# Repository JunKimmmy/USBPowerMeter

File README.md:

# USB-C Power Meter

A compact USB-C passthrough power meter that displays real-time voltage, current, and power on an integrated 128×64 OLED screen. It sits inline between a USB-C charger and a device — all USB signals pass through transparently while the onboard MCU samples the INA238 power monitor and drives the display.

---

## Features

- **Real-time readout** — voltage, current, and power updated continuously
- **Rolling graphs** — 128-sample circular-buffer plots for current and power with live, average, and peak annotations
- **Running averages** — displayed in the footer of the main meter screen
- **Boot animation** and **dancing-banana easter egg**
- **Buzzer** with user-configurable tones and mute toggle
- **Power switch** and **navigation buttons** for menu control
- Full USB-C signal passthrough (VBUS + data lines)

---

## Specifications

| Parameter | Value |
|-----------|-------|
| Input voltage range | 0.3 V – 48 V |
| Max continuous current | 5 A |
| ADC resolution | 16-bit (INA238) |
| Display | 128×64 OLED (SSD1315), I²C |
| MCU | STM32G030K6T6 (LQFP-32) |
| MCU/peripheral supply | 3.3 V buck from VBUS |
| OLED supply | 3.8 V boost |
| Passthrough | USB-C male + USB-C female |

---

## PCB

Designed in **KiCad 10**. All custom symbols and footprints are in `libs/`.

### Key ICs

| IC | Function |
|----|----------|
| INA238 | 16-bit high-precision power/current/voltage monitor (shunt + bus voltage) |
| STM32G030K6T6 | Measurement processing, graph engine, display control |
| SSD1315 | 128×64 OLED controller (I²C) |
| LMR36006 | VBUS-to-3.3 V synchronous buck regulator |
| DGS0010A | 3.8 V boost supply for OLED |

---

## Enclosure

3D-printable enclosure designed in OnShape:
[View in OnShape](https://cad.onshape.com/documents/12768789c7e8d715e02a9c44/w/91224a42db391f032592c489/e/40e560f0614cc0d05faddfcd?renderMode=0&uiState=6a30851d7d6de7ff176b633c)

---

## Build Process

All components were **hand-soldered**. Firmware was flashed over SWD using an **ST-Link V3 Mini**.

### Videos

| Video | Description |
|-------|-------------|
| [PCB Assembly](videos/pcb-assembly.mp4) | Hand-soldering all components onto the board |
| [Display Testing](videos/display-testing.mp4) | OLED display bring-up and meter UI |
| [Buzzer Testing](videos/buzzer-testing.mp4) | Buzzer tone testing |

---

## Testing

The meter was tested by powering a **mini hotplate** (~20 V supply). The power graph clearly shows the hotplate's heating element ramping up linearly from 0 W as it heats, plateauing around **42 W** once it reaches temperature, then dropping sharply when switched off.

---

## Firmware

Written in C using STM32CubeIDE with the STM32 HAL. Targets the STM32G030K6T6.

### Display Modes

| Mode | Description |
|------|-------------|
| **Main Meter** | Two-column header (VOLT / AMPS), large 2× readout, full-width power row, footer with running averages |
| **Current Graph** | 128-sample rolling plot of current (mA), dashed line = running average, header shows live + avg + peak |
| **Power Graph** | Same layout as current graph but for power (mW) |

Navigate between modes with the onboard buttons.

### Source Modules

| File | Purpose |
|------|---------|
| `main.c` | HAL init, main loop, buzzer tone engine |
| `meter.c` | Display screens, graph circular buffer, button debounce |
| `oled.c` | SSD1315 OLED driver (I²C, page-mode framebuffer) |
| `ina238.c` | INA238 driver — shunt/bus voltage, current, power registers |
| `boot.c` | Animated boot screen |
| `banana.c / banana_frames.c` | Dancing-banana easter egg animation |
| `generate_frames.py` | Converts 249×246 GIF PROGMEM bitmaps to SSD1315 page-format C arrays |

### Building & Flashing

1. Open `Firmware/ST/` in **STM32CubeIDE**
2. Build (Ctrl+B) — targets STM32G030K6T6, `STM32G030K6TX_FLASH.ld`
3. Connect **ST-Link V3 Mini** to the SWD header and flash

---

## Repository Structure

```
USBpowermeter.kicad_pro       KiCad project
USBpowermeter.kicad_sch       Schematic
USBpowermeter.kicad_pcb       PCB layout
libs/
  Library.kicad_sym           Custom schematic symbols
  Library.pretty/             Custom footprints
  3dmodels/                   STEP models for 3D viewer
Firmware/ST/
  Core/Src/                   Application source (C)
  Core/Inc/                   Application headers
  Drivers/                    STM32 HAL + CMSIS
  generate_frames.py          Bitmap conversion tool
images/                       PCB renders, enclosure CAD, real photos
videos/                       Assembly and testing footage
```

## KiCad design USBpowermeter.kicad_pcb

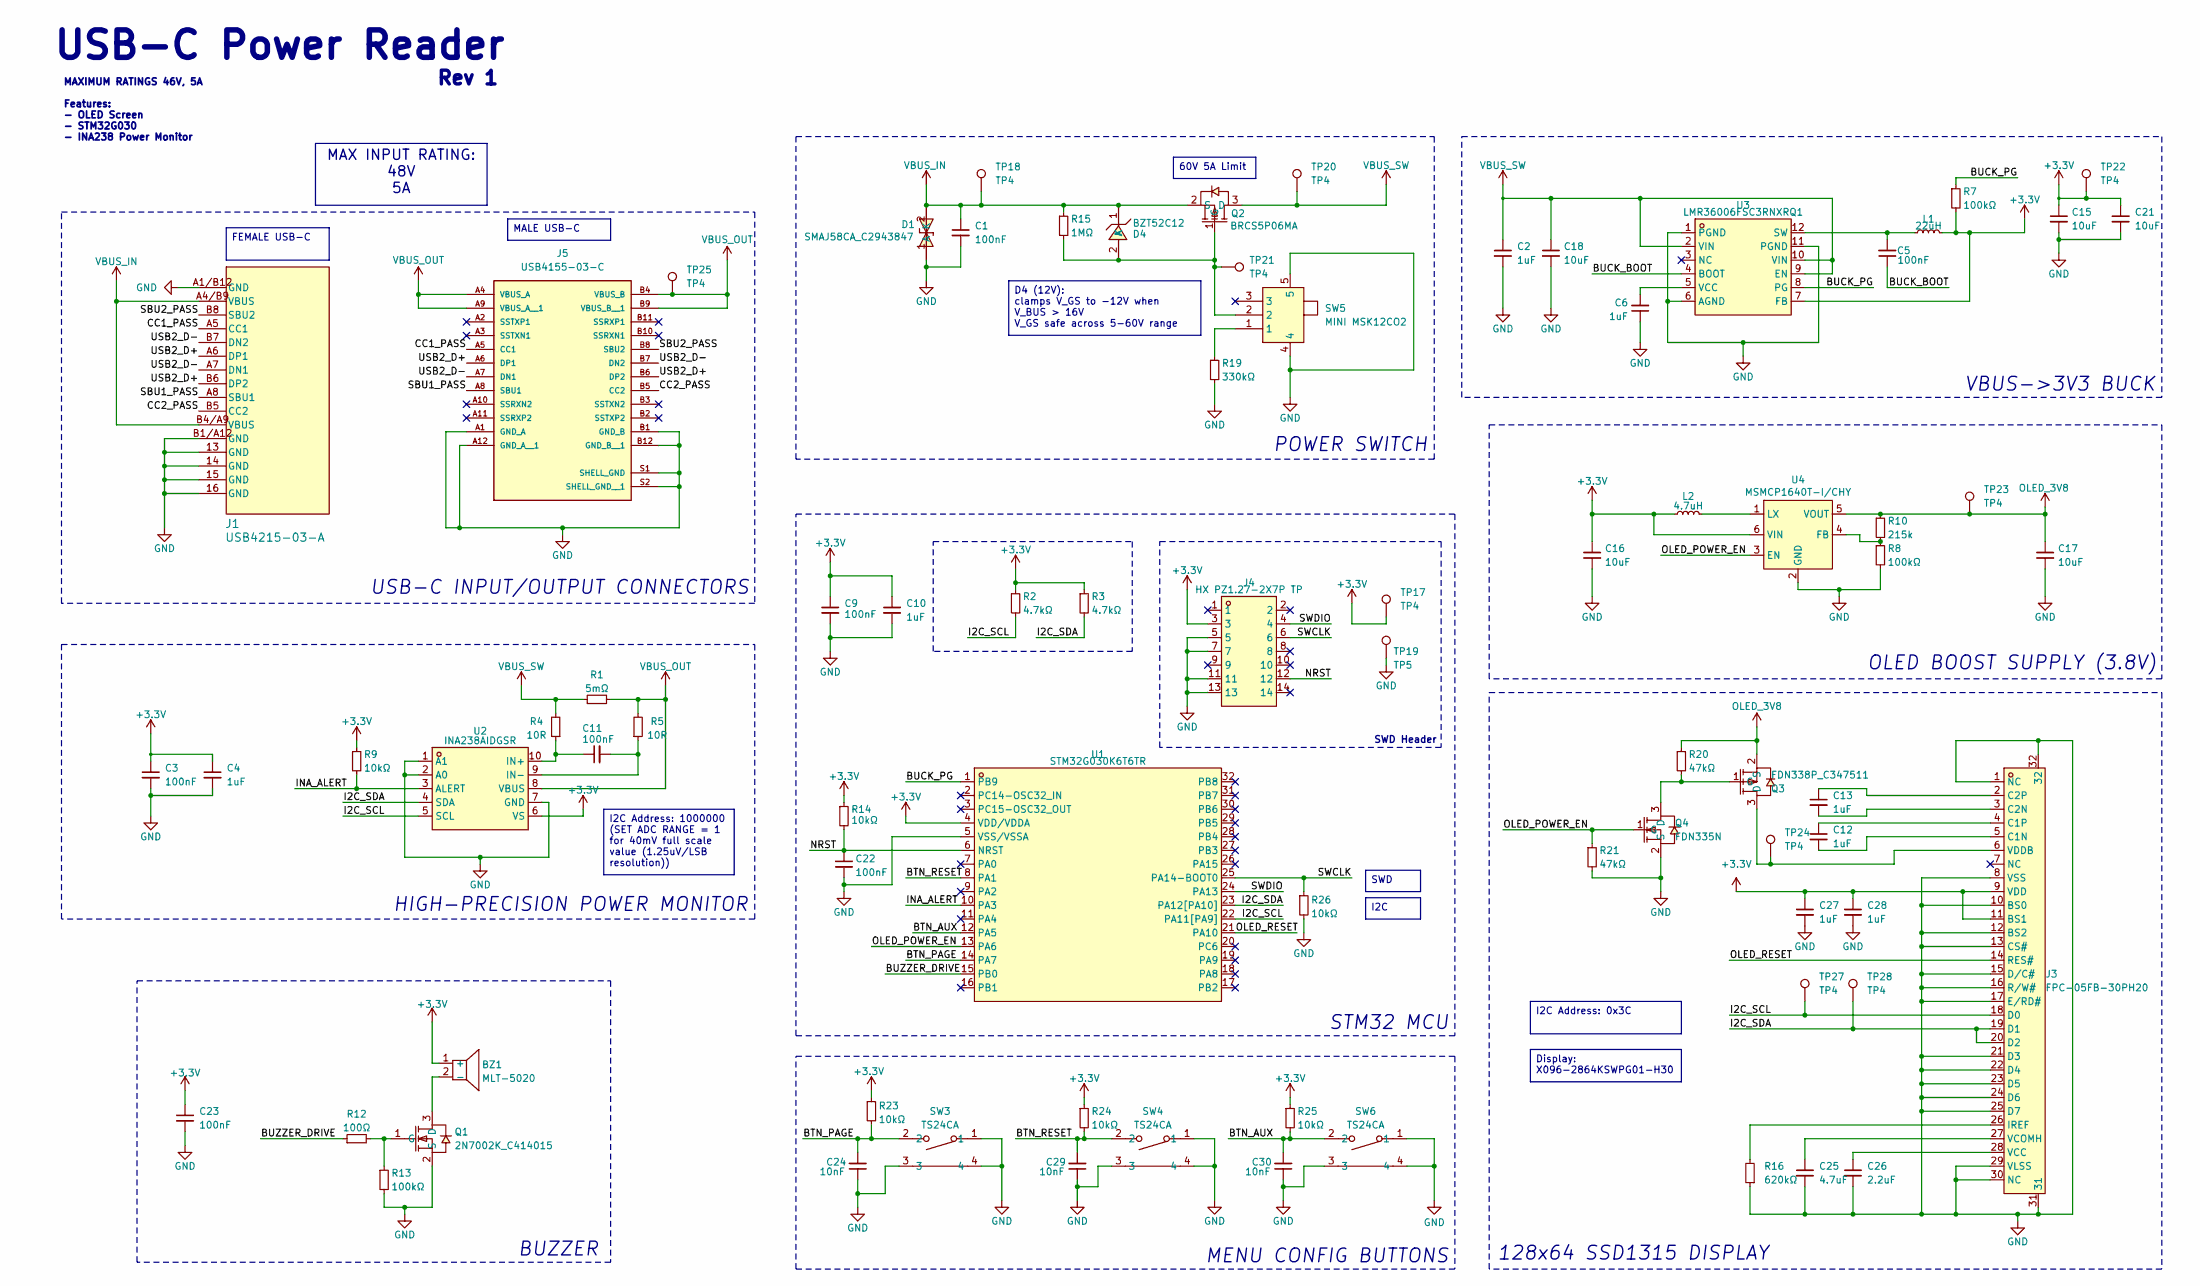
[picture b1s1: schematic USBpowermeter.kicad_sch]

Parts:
BZ1: MLT-5020; BUZ-SMD_L5.0-W5.5-P4.60; LCSC Part C94598
C1: 100nF; C_0603_1608Metric; LCSC Part C77058
C2, C4, C6, C10, C12, C13, C27, C28: 1uF; C_0402_1005Metric; LCSC Part C42371686
C3, C5, C9, C11, C22, C23: 100nF; C_0402_1005Metric; LCSC Part C343042
C15, C16, C17, C21: 10uF; C_0402_1005Metric; LCSC Part C15525
C18: 10uF; C_0805_2012Metric; LCSC Part C22367830
C24, C29, C30: 10nF; C_0402_1005Metric; LCSC Part C22400107
C25: 4.7uF; C_0402_1005Metric; LCSC Part C318563
C26: 2.2uF; C_0402_1005Metric; LCSC Part C12530
D1: SMAJ58CA_C2943847; SMA_L4.2-W2.6-LS5.0-BI; LCSC Part C148235
D4: BZT52C12; SOD-123_L2.7-W1.6-LS3.7-RD; LCSC Part C19077410
J1: USB4215-03-A; CONN_8p94X6p5X3p16_12L_GCC; LCSC Part C37616412
J3: FPC-05FB-30PH20; FPC-SMD_30P-P0.50_FPC-05FB-30PH20; LCSC Part C2856833
J4: HX PZ1.27-2X7P TP; HDR-SMD_14P-P1.27_HX-PZ1.27-2X7P-TP; LCSC Part C41376039
J5: USB4155-03-C; GCT_USB4155-03-C_REVA; PARTREV A; LCSC Part ORDER ON DIGIKEY
L1: 22uH; L_APV_ANR3015; LCSC Part C6364792
L2: 4.7uH; L_0603_1608Metric; LCSC Part C295681
Q1: 2N7002K_C414015; SOT-23-3; LCSC Part C8545
Q2: BRCS5P06MA; SOT-23-3_L2.9-W1.3-P1.90-LS2.4-BR; LCSC Part C914070
Q3: FDN338P_C347511; SOT-23-3; LCSC Part C24855
Q4: FDN335N; SOT-23-3; LCSC Part C241804
R1: 5mΩ; R_1206_3216Metric; LCSC Part C2988648
R2, R3: 4.7kΩ; R_0402_1005Metric; LCSC Part C105871
R4, R5: 10R; R_0402_1005Metric; LCSC Part C2906862
R7, R8, R13: 100kΩ; R_0402_1005Metric; LCSC Part C2906859
R9, R14, R23, R24, R25, R26: 10kΩ; R_0402_1005Metric; LCSC Part C2906861
R10: 215k; R_0402_1005Metric; LCSC Part C3013158
R12: 100Ω; R_0402_1005Metric; LCSC Part C2906860
R15: 1MΩ; R_0402_1005Metric; LCSC Part C2909328
R16: 620kΩ; R_0402_1005Metric; LCSC Part C2909373
R19: 330kΩ; R_0402_1005Metric; LCSC Part C2909349
R20, R21: 47kΩ; R_0402_1005Metric; LCSC Part C2906872
SW3, SW4, SW6: TS24CA; SW-SMD_2P-TS24CA; LCSC Part C393942
SW5: MINI MSK12CO2; SW-SMD_MSK12CO2; LCSC Part C2681570
TP17, TP18, TP20, TP21, TP22, TP23, TP24, TP25, TP27, TP28: TP4; TestPoint_Pad_D1.0mm
TP19: TP5; TestPoint_Pad_D1.0mm
U1: STM32G030K6T6TR; LQFP-32_L7.0-W7.0-P0.80-LS9.0-BL; LCSC Part C724043
U2: INA238AIDGSR; VSSOP-10_L3.0-W3.0-P0.50-LS4.9-BL; LCSC Part C2868250
U3: LMR36006FSC3RNXRQ1; VQFN-12_L3.0-W2.0-P0.65-BL_TI_RNX; LCSC Part C1850337
U4: MSMCP1640T-I/CHY; SOT-23-6; LCSC Part C49208392

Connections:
+3.3V: BZ1.1 (+), C3.1, C4.1, C9.1, C10.1, C15.1, C16.1, C21.1, C23.1, C27.1, C28.1, J3.9 (VDD), J3.11 (BS1), J4.3, L1.2, L2.1, R2.1, R3.1, R7.2, R9.1, R14.1, R23.1, R24.1, R25.1, TP17.1, TP22.1 (1_1), U1.4 (VDD/VDDA), U2.6 (VS), U3.7 (FB), U4.6 (VIN)
/BTN_AUX: C30.2, R25.2, SW6.2, U1.12 (PA5)
/BTN_PAGE: C24.2, R23.2, SW3.2, U1.14 (PA7)
/BTN_RESET: C29.2, R24.2, SW4.2, U1.8 (PA1)
/BUCK_BOOT: C5.1, U3.4 (BOOT)
/BUCK_PG: R7.1, U1.1 (PB9), U3.8 (PG)
/BUZZER_DRIVE: R12.1, U1.15 (PB0)
/CC1_PASS: J1.A5 (CC1), J5.A5 (CC1)
/CC2_PASS: J1.B5 (CC2), J5.B5 (CC2)
/I2C_SCL: J3.18 (D0), R2.2, TP27.1 (1_1), U1.22 (PA11[PA9]), U2.5 (SCL)
/I2C_SDA: J3.19 (D1), J3.20 (D2), R3.2, TP28.1 (1_1), U1.23 (PA12[PA10]), U2.4 (SDA)
/INA_ALERT: R9.2, U1.10 (PA3), U2.3 (ALERT)
/NRST: C22.1, J4.12, R14.2, U1.6 (NRST)
/OLED_POWER_EN: Q4.1 (G), R21.1, U1.13 (PA6), U4.3 (EN)
/OLED_RESET: J3.14 (RES#), U1.21 (PA10)
/SBU1_PASS: J1.A8 (SBU1), J5.A8 (SBU1)
/SBU2_PASS: J1.B8 (SBU2), J5.B8 (SBU2)
/SWCLK: J4.6, R26.1, U1.25 (PA14-BOOT0)
/SWDIO: J4.4, U1.24 (PA13)
/USB2_D+: J1.A6 (DP1), J1.B6 (DP2), J5.A6 (DP1), J5.B6 (DP2)
/USB2_D-: J1.A7 (DN1), J1.B7 (DN2), J5.A7 (DN1), J5.B7 (DN2)
GND: C1.2, C2.2, C3.2, C4.2, C6.1, C9.2, C10.2, C15.2, C16.2, C17.2, C18.2, C21.2, C22.2, C23.2, C24.1, C25.2, C26.2, C27.2, C28.2, C29.1, C30.1, D1.1 (K), J1.13 (GND), J1.14 (GND), J1.15 (GND), J1.16 (GND), J1.A1/B12 (GND), J1.B1/A12 (GND), J3.1 (NC), J3.8 (VSS), J3.10 (BS0), J3.12 (BS2), J3.13 (CS#), J3.15 (D/C#), J3.16 (R/W#), J3.17 (E/RD#), J3.21 (D3), J3.22 (D4), J3.23 (D5), J3.24 (D6), J3.25 (D7), J3.29 (VLSS), J3.30 (NC), J3.31, J3.32, J4.5, J4.7, J4.11, J4.13, J5.A1 (GND_A), J5.A12 (GND_A__1), J5.B1 (GND_B), J5.B12 (GND_B__1), J5.S1 (SHELL_GND), J5.S2 (SHELL_GND__1), Q1.2 (S), Q4.2 (S), R8.2, R13.2, R16.1, R19.2, R21.2, R26.2, SW3.1, SW3.3, SW3.4, SW4.1, SW4.3, SW4.4, SW5.4, SW5.5, SW6.1, SW6.3, SW6.4, TP19.1 (1_1), U1.5 (VSS/VSSA), U2.1 (A1), U2.2 (A0), U2.7 (GND), U3.1 (PGND), U3.6 (AGND), U3.11 (PGND), U4.2 (GND); also elsewhere on the board
unnamed: BZ1.2 (-), Q1.3 (D)
unnamed: D4.2 (A), Q2.1 (G), R15.2, SW5.2, TP21.1 (1_1)
unnamed: C12.2, J3.5 (C1N)
unnamed: C12.1, J3.4 (C1P)
unnamed: C13.2, J3.3 (C2N)
unnamed: C13.1, J3.2 (C2P)
unnamed: J3.26 (IREF), R16.2
unnamed: C26.1, J3.28 (VCC)
unnamed: C25.1, J3.27 (VCOMH)
unnamed: J3.6 (VDDB), Q3.3 (D), TP24.1 (1_1)
unnamed: Q1.1 (G), R12.2, R13.1
unnamed: Q3.1 (G), Q4.3 (D), R20.2
unnamed: R19.1, SW5.1
unnamed: C11.1, R4.1, U2.10 (IN+)
unnamed: C11.2, R5.1, U2.9 (IN-)
unnamed: C5.2, L1.1, U3.12 (SW)
unnamed: C6.2, U3.5 (VCC)
unnamed: R8.1, R10.2, U4.4 (FB)
unnamed: L2.2, U4.1 (LX)
OLED_3V8: C17.1, Q3.2 (S), R10.1, R20.1, TP23.1 (1_1), U4.5 (VOUT)
VBUS_IN: C1.1, D1.2 (A), D4.1 (K), J1.A4/B9 (VBUS), J1.B4/A9 (VBUS), Q2.2 (S), R15.1, TP18.1 (1_1)
VBUS_OUT: J5.A4 (VBUS_A), J5.A9 (VBUS_A__1), J5.B4 (VBUS_B), J5.B9 (VBUS_B__1), R1.2, R5.2, TP25.1 (1_1), U2.8 (VBUS)
VBUS_SW: C2.1, C18.1, Q2.3 (D), R1.1, R4.2, TP20.1 (1_1), U3.2 (VIN), U3.9 (EN), U3.10 (VIN)

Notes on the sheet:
BUZZER
USB-C INPUT/OUTPUT CONNECTORS
STM32 MCU
POWER SWITCH
HIGH-PRECISION POWER MONITOR
SWD Header
OLED BOOST SUPPLY (3.8V)
VBUS->3V3 BUCK
MAXIMUM RATINGS 46V, 5A Features: - OLED Screen - STM32G030 - INA238 Power Monitor
Rev 1
128x64 SSD1315 DISPLAY
MENU CONFIG BUTTONS
USB-C Power Reader
60V 5A Limit
D4 (12V): clamps V_GS to -12V when V_BUS > 16V V_GS safe across 5-60V range
I2C Address: 0x3C
Display: X096-2864KSWPG01-H30
FEMALE USB-C
I2C
SWD
MAX INPUT RATING: 48V 5A
I2C Address: 1000000 (SET ADC RANGE = 1 for 40mV full scale value (1.25uV/LSB resolution))
MALE USB-C

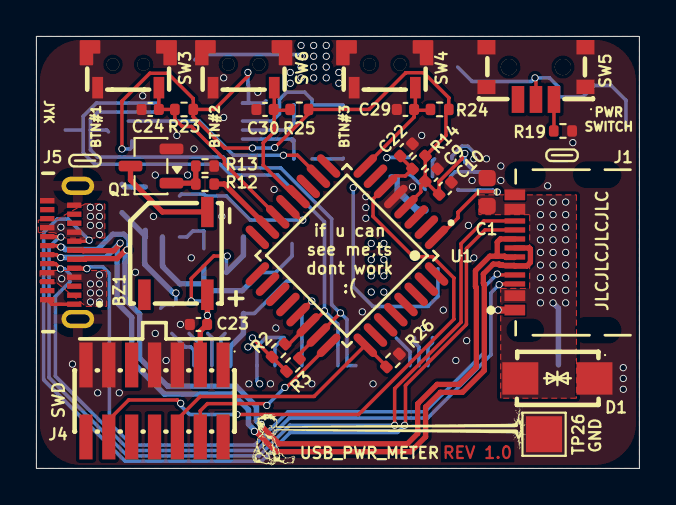
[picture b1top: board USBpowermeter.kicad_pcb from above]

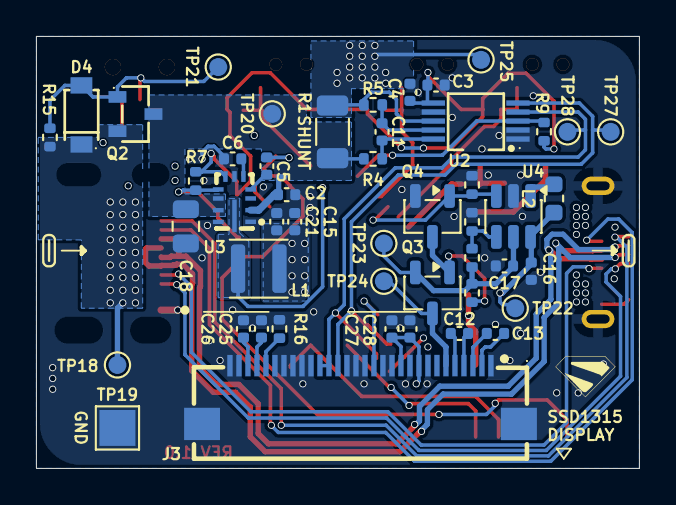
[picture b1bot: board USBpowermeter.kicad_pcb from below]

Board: 4 copper layers, 33.5 x 24.0 mm, 78 parts (48 on the bottom side), 45 nets.

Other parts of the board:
TP26: TP5; TestPoint_Pad_2.0x2.0mm

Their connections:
GND: TP26.1 (1_1); also elsewhere on the board

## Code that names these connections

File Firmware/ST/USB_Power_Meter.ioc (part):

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Mcu.Name=STM32G030K(6-8)Tx
Mcu.Package=LQFP32
Mcu.UserName=STM32G030K6Tx
PA1.GPIOParameters=GPIO_PuPd,GPIO_Label
PA1.GPIO_Label=BTN_RESET
PA1.GPIO_PuPd=GPIO_PULLUP
PA1.Signal=GPIO_Input
PA10.GPIOParameters=GPIO_Label
PA10.GPIO_Label=OLED_RESET
PA10.Signal=GPIO_Output
PA11\ [PA9].Mode=I2C
PA11\ [PA9].Signal=I2C2_SCL
PA12\ [PA10].Mode=I2C
PA12\ [PA10].Signal=I2C2_SDA
PA13.Mode=Serial_Wire
PA13.Signal=SYS_SWDIO
PA14-BOOT0.Mode=Serial_Wire
PA14-BOOT0.Signal=SYS_SWCLK
PA3.GPIOParameters=GPIO_Label
PA3.GPIO_Label=INA_ALERT
PA3.Signal=GPIO_Input
PA5.GPIOParameters=GPIO_PuPd,GPIO_Label
PA5.GPIO_Label=BTN_AUX
PA5.GPIO_PuPd=GPIO_PULLUP
PA5.Signal=GPIO_Input
PA6.GPIOParameters=GPIO_Label
PA6.GPIO_Label=OLED_POWER_EN
PA6.Signal=GPIO_Output
PA7.GPIOParameters=GPIO_PuPd,GPIO_Label
PA7.GPIO_Label=BTN_PAGE
PA7.GPIO_PuPd=GPIO_PULLUP
PA7.Signal=GPIO_Input
PB0.Signal=S_TIM3_CH3
PB9.GPIOParameters=GPIO_Label
PB9.GPIO_Label=BUCK_PG
PB9.Signal=GPIO_Input
RCC.HSE_VALUE=8000000
RCC.SYSCLKFreq_VALUE=16000000
board=custom

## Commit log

2026-05-17 Schematic Updates
2026-05-17 Schem update
2026-05-18 schematic changes
2026-05-23 push layout
2026-05-23 Fabrication Push
2026-05-23 Final Fab Commit
2026-06-01 Final Fabrication Commit
2026-06-01 Add images to README for better visualization
    Added images to enhance the README with visual content.
2026-06-15 push
2026-06-15 firmware
2026-06-16 Clean up repo and expand README
    - Remove build artifacts (Debug/) and Claude settings from tracking
    - Update .gitignore to exclude Debug/, .claude/, and IDE workspace files
    - Rewrite README with full feature list, display modes, firmware module table, enclosure OnShape link, and build instructions
    - Stage latest firmware changes (banana.c, main.c, meter.c)
2026-06-16 Add images and videos, update README with media
2026-06-16 Add final photos and expand build process section
2026-06-16 Restore original hero photos and add PCB+enclosure as third
2026-06-16 Add plugged-in display photo to hero section
2026-06-16 Add testing section with hotplate photos, swap hero image
